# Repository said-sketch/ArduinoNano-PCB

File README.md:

# Arduino Nano PCB (KiCad Project)

Custom PCB design for **Arduino Nano** created with **KiCad**.  
This project includes the schematic, PCB layout, and production files for manufacturing.

---

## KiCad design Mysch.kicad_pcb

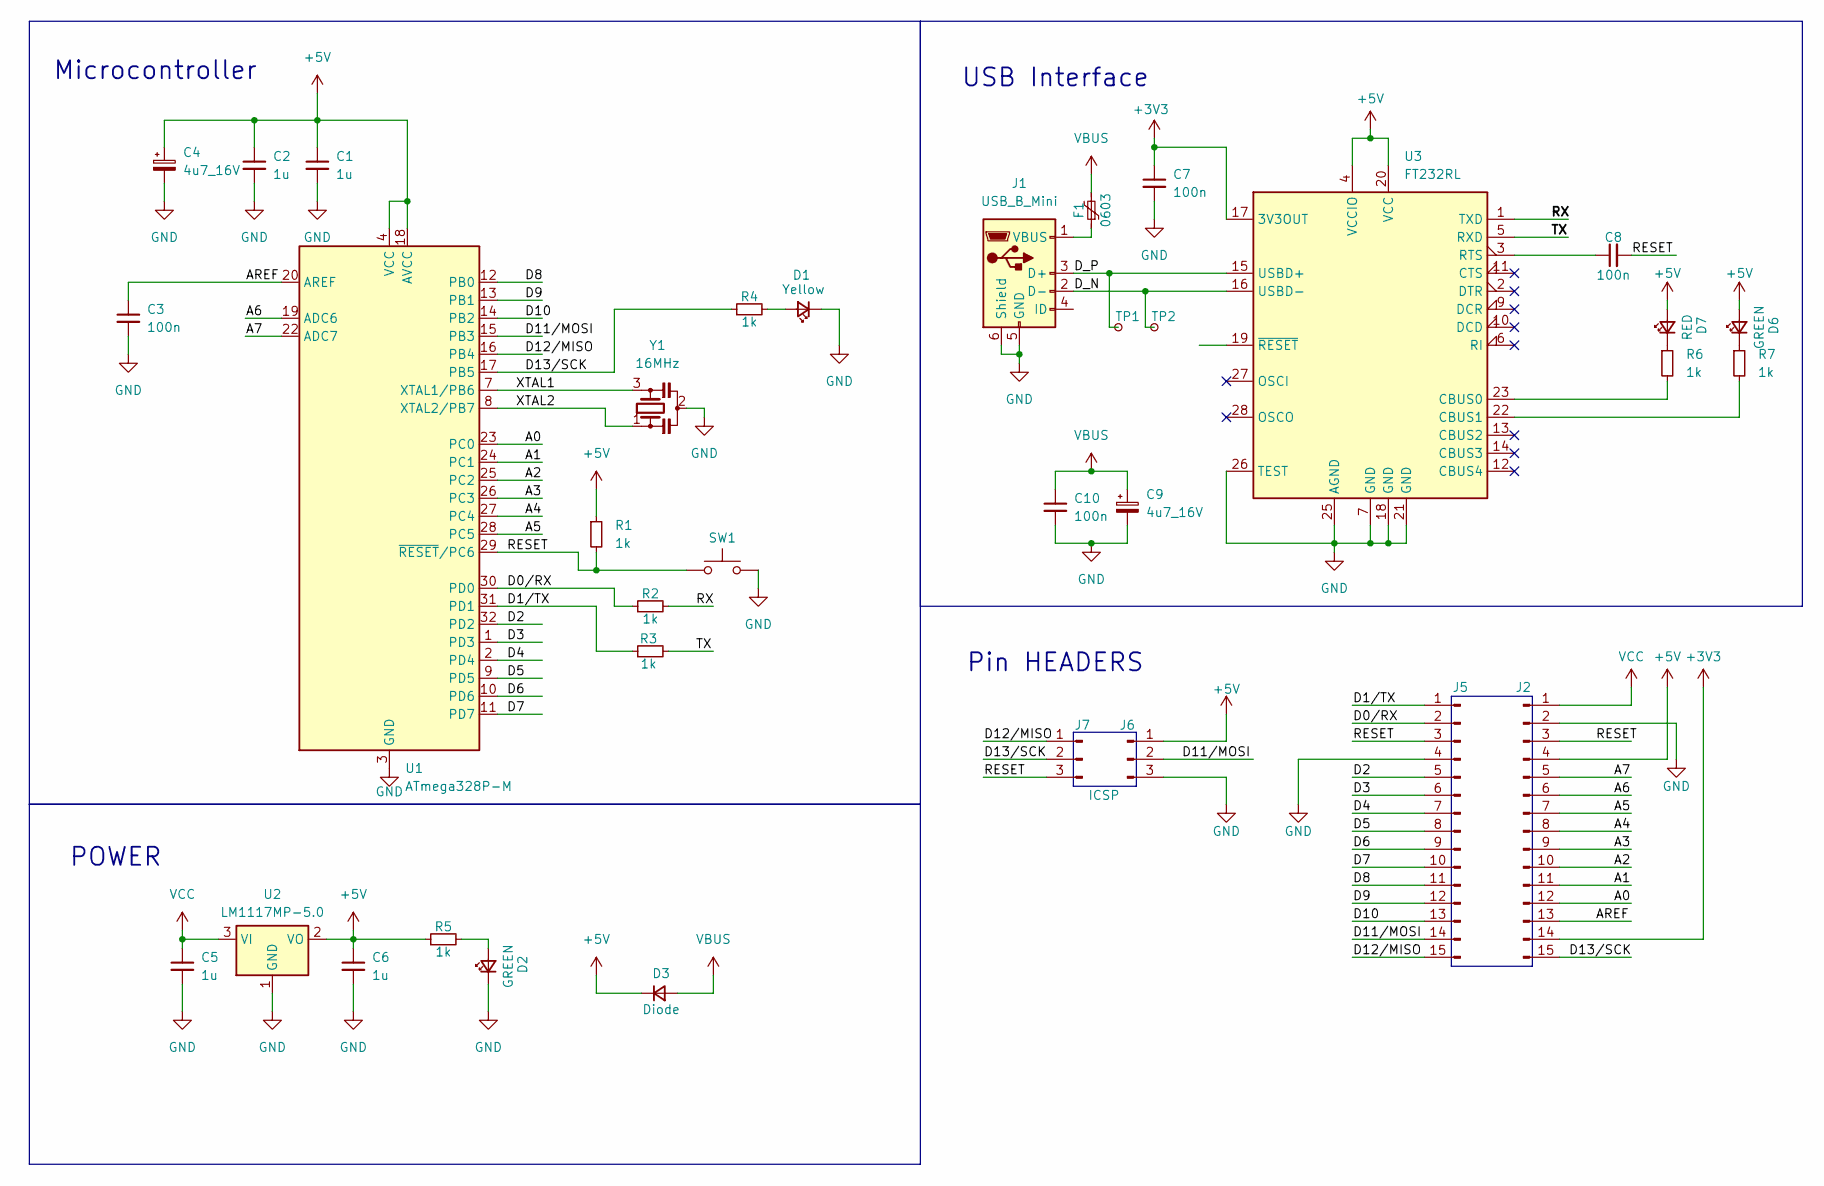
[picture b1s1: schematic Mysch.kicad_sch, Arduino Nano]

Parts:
C1, C2, C5, C6: 1u; C_0603_1608Metric
C3, C7, C8, C10: 100n; C_0603_1608Metric
C4, C9: 4u7_16V; CP_EIA-3216-10_Kemet-I
D1: Yellow; LED_0805_2012Metric
D2, D6: GREEN; LED_0805_2012Metric
D3: Diode; D_MicroSMP_AK
D7: RED; LED_0805_2012Metric
F1: 0603; D_0805_2012Metric
J1: USB_B_Mini; USB_Mini-B_Wuerth_65100516121_Horizontal
J2, J5: Conn_01x15_Pin; PinHeader_1x15_P2.54mm_Vertical
J6, J7: ICSP; PinHeader_1x03_P2.54mm_Vertical
R1, R2, R3, R4, R5, R6, R7: 1k; D_0603_1608Metric
SW1: SW_Push; Panasonic_EVQPUK_EVQPUB
TP1, TP2: TestPoint_Small; TestPoint_Pad_D1.0mm
U1: ATmega328P-M; QFN-32-1EP_5x5mm_P0.5mm_EP3.1x3.1mm
U2: LM1117MP-5.0; SOT-223-3_TabPin2
U3: FT232RL; SSOP-28_5.3x10.2mm_P0.65mm
Y1: 16MHz; Resonator_SMD_Murata_CSTxExxV-3Pin_3.0x1.1mm

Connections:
+3V3: C7.1, J2.14, U3.17 (3V3OUT)
+5V: C1.1, C2.1, C4.1, C6.1, D3.1 (K), D6.2 (A), D7.2 (A), J2.4, J6.1, R1.1, R5.1, U1.4 (VCC), U1.6 (VCC), U1.18 (AVCC), U2.2 (VO), U3.4 (VCCIO), U3.20 (VCC)
/A0: J2.12, U1.23 (PC0)
/A1: J2.11, U1.24 (PC1)
/A2: J2.10, U1.25 (PC2)
/A3: J2.9, U1.26 (PC3)
/A4: J2.8, U1.27 (PC4)
/A5: J2.7, U1.28 (PC5)
/A6: J2.6, U1.19 (ADC6)
/A7: J2.5, U1.22 (ADC7)
/AREF: C3.1, J2.13, U1.20 (AREF)
/D0/RX: J5.2, R2.1, U1.30 (PD0)
/D1/TX: J5.1, R3.1, U1.31 (PD1)
/D2: J5.5, U1.32 (PD2)
/D3: J5.6, U1.1 (PD3)
/D4: J5.7, U1.2 (PD4)
/D5: J5.8, U1.9 (PD5)
/D6: J5.9, U1.10 (PD6)
/D7: J5.10, U1.11 (PD7)
/D8: J5.11, U1.12 (PB0)
/D9: J5.12, U1.13 (PB1)
/D10: J5.13, U1.14 (PB2)
/D11/MOSI: J5.14, J6.2, U1.15 (PB3)
/D12/MISO: J5.15, J7.1, U1.16 (PB4)
/D13/SCK: J2.15, J7.2, R4.1, U1.17 (PB5)
/D_N: J1.2 (D-), TP2.1, U3.16 (USBD-)
/D_P: J1.3 (D+), TP1.1, U3.15 (USBD+)
/RESET: C8.2, J2.3, J5.3, J7.3, R1.2, SW1.1, U1.29 (~RESET/PC6)
/RX: R2.2, U3.1 (TXD)
/TX: R3.2, U3.5 (RXD)
/XTAL1: U1.7 (XTAL1/PB6), Y1.3
/XTAL2: U1.8 (XTAL2/PB7), Y1.1
GND: C1.2, C2.2, C3.2, C4.2, C5.2, C6.2, C7.2, C9.2, C10.2, D1.1 (K), D2.1 (K), J1.5 (GND), J1.6 (Shield), J2.2, J5.4, J6.3, SW1.2, U1.3 (GND), U1.5 (GND), U1.21 (GND), U1.33 (GND), U2.1 (GND), U3.7 (GND), U3.18 (GND), U3.21 (GND), U3.25 (AGND), U3.26 (TEST), Y1.2
unnamed: D1.2 (A), R4.2
unnamed: D2.2 (A), R5.2
unnamed: D6.1 (K), R7.1
unnamed: D7.1 (K), R6.1
unnamed 37: F1.1, J1.1 (VBUS); also elsewhere on the board
unnamed: R6.2, U3.23 (CBUS0)
unnamed: R7.2, U3.22 (CBUS1)
unnamed: C8.1, U3.3 (RTS)
VBUS: C9.1, C10.1, D3.2 (A), F1.2; also elsewhere on the board
VCC: C5.1, J2.1, U2.3 (VI)

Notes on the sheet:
Microcontroller
USB Interface
Pin HEADERS
POWER

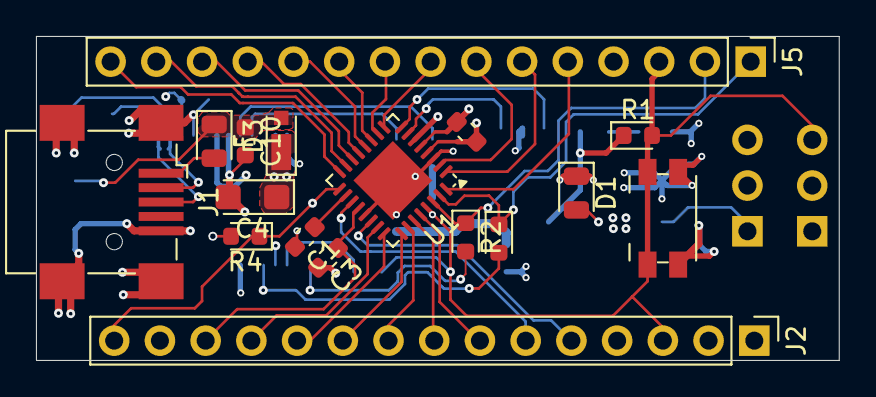
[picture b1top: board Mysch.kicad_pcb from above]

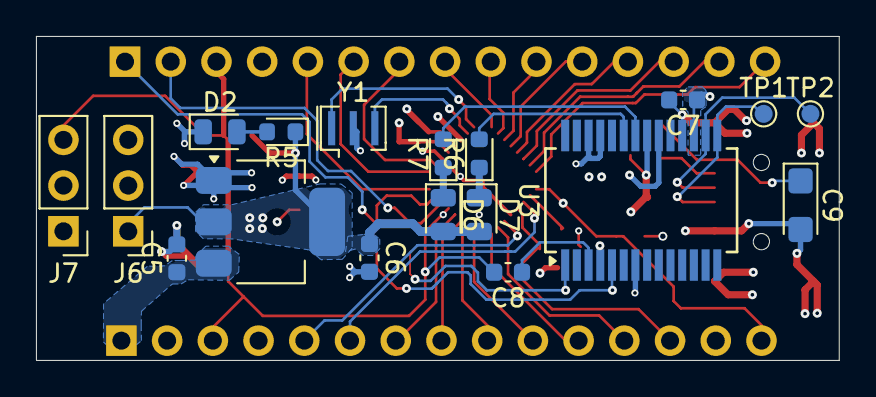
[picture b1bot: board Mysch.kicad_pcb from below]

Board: 4 copper layers, 44.6 x 18.0 mm, 35 parts (18 on the bottom side), 43 nets.

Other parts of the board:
F: 0603; D_0805_2012Metric

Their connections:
unnamed 37: F.1; also elsewhere on the board
VBUS: F.2; also elsewhere on the board

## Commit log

2025-08-29 Initial commit - Arduino Nano PCB
2025-08-29 Add .gitignore to ignore backups and temp files
2025-08-29 Add project README with description and preview
